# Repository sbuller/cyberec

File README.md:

# cyberec

Embedded Controller and BMS for Cyberdecks

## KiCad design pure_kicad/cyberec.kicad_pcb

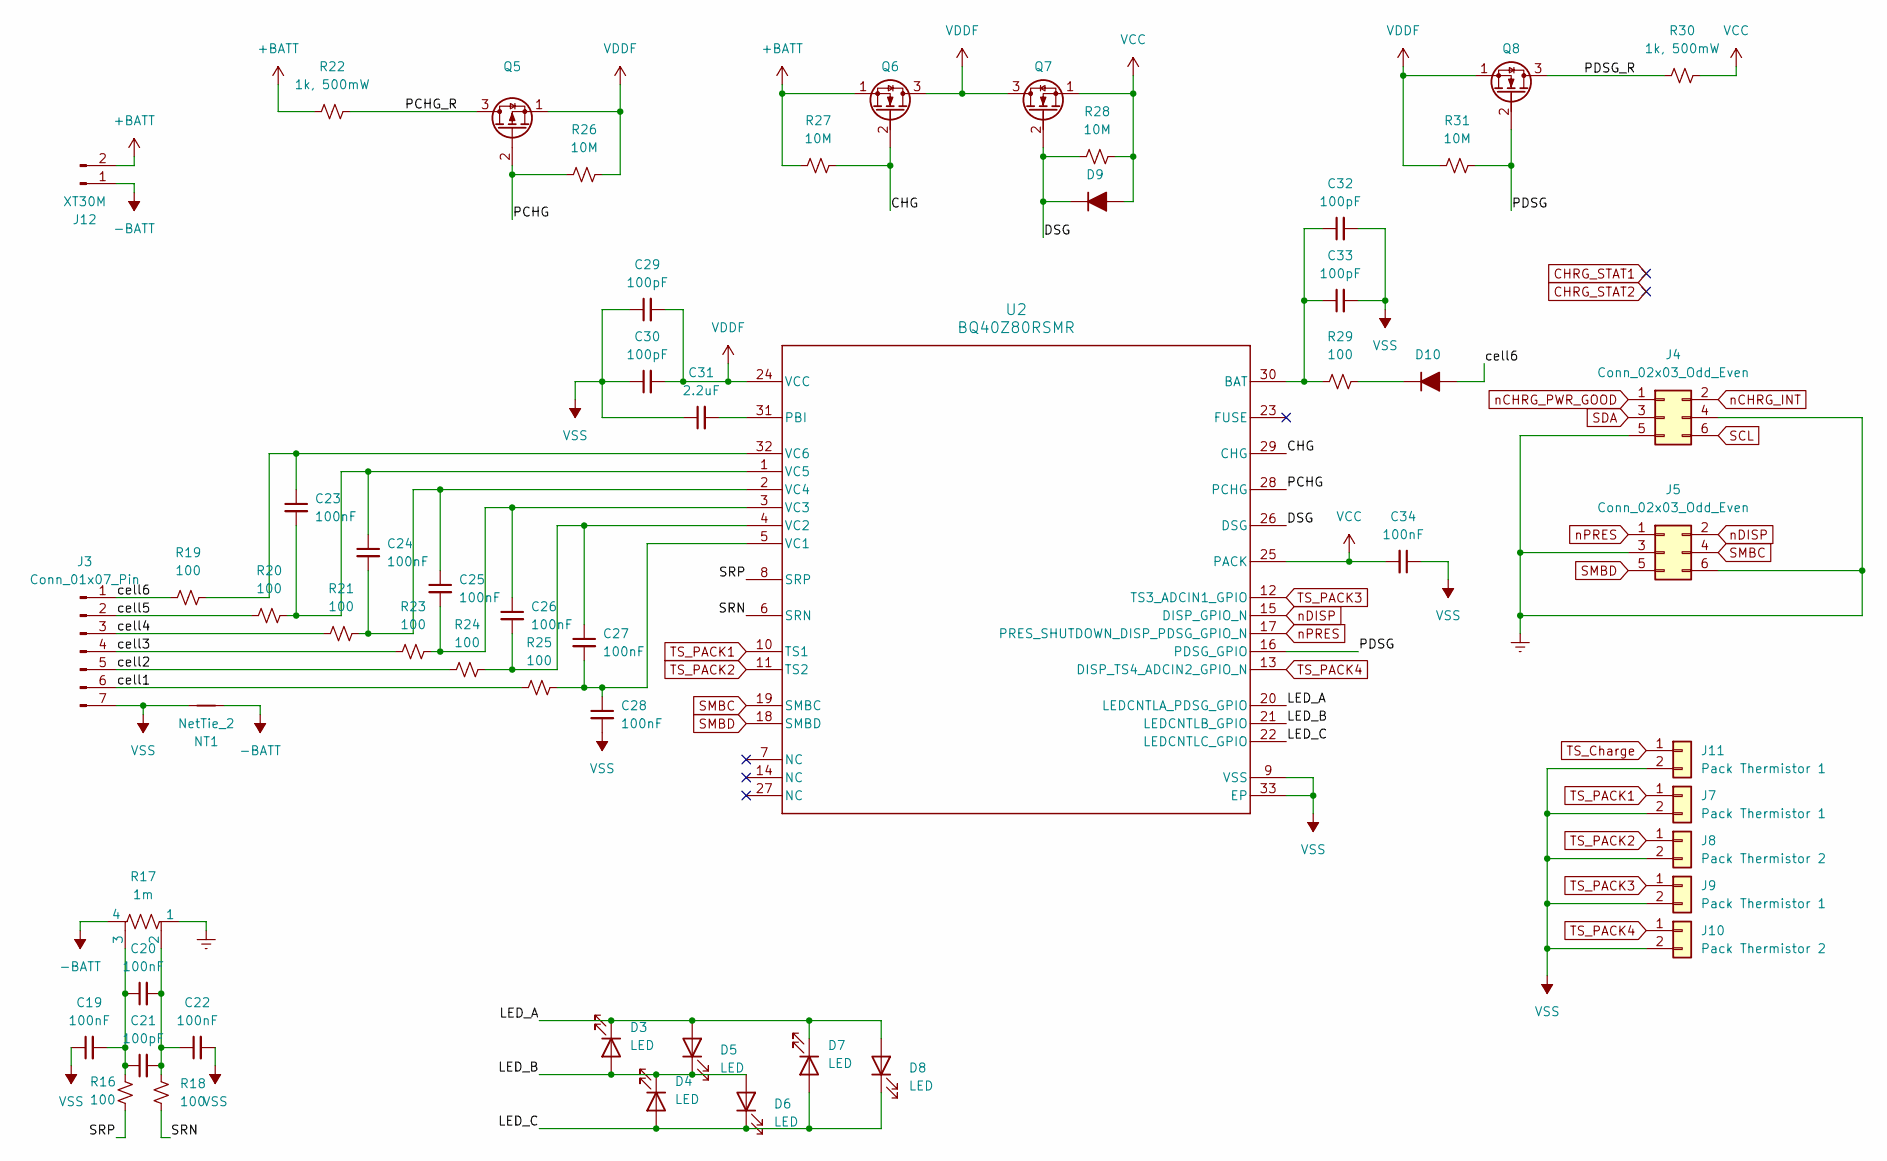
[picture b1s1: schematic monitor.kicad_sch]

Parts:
C19, C20, C22, C23, C24, C25, C26, C27, C28, C34: 100nF; C_0603_1608Metric_Pad1.08x0.95mm_HandSolder
C21, C29, C30, C32, C33: 100pF; C_0603_1608Metric_Pad1.08x0.95mm_HandSolder
C31: 2.2uF; C_0603_1608Metric_Pad1.08x0.95mm_HandSolder
D3, D4, D5, D6, D7, D8: LED; LED_0603_1608Metric_Pad1.05x0.95mm_HandSolder
D9, D10: 1N4001; D_SOD-123F
J3: Conn_01x07_Pin; JST_XH_B7B-XH-AM_1x07_P2.50mm_Vertical
J4, J5: Conn_02x03_Odd_Even; PinHeader_2x03_P1.27mm_Vertical
J7, J9, J11: Pack Thermistor 1; PinHeader_1x02_P2.00mm_Vertical
J8, J10: Pack Thermistor 2; PinHeader_1x02_P2.00mm_Vertical
J12: XT30M; AMASS_XT30U-M_1x02_P5.0mm_Vertical
NT1: NetTie_2; NetTie-2_SMD_Pad2.0mm
Q5: Q_PMOS_SGD; DFN-8_L3.0-W3.0-P0.65-BL-4
Q6, Q7, Q8: Q_NMOS_DGS; DFN-8_L3.0-W3.0-P0.65-BL-4
R16, R18, R19, R20, R21, R23, R24, R25, R29: 100; R_0603_1608Metric_Pad0.98x0.95mm_HandSolder
R17: 1m; R1206-sense-handsolder
R22, R30: 1k, 500mW; R_1210_3225Metric_Pad1.30x2.65mm_HandSolder
R26, R27, R28, R31: 10M; R_0402_1005Metric_Pad0.72x0.64mm_HandSolder
U2: BQ40Z80RSMR; RSM0032A-IPC_A

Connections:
+BATT: J12.2, Q6.1 (S), R22.2, R27.2
-BATT: J12.1, NT1.2, R17.4
/Battery Monitor/CHG: Q6.2 (G), R27.1, U2.29 (CHG)
/Battery Monitor/DSG: D9.1 (K), Q7.2 (G), R28.2, U2.26 (DSG)
/Battery Monitor/LED_A: D3.1 (K), D5.2 (A), D7.1 (K), D8.2 (A), U2.20 (LEDCNTLA_PDSG_GPIO)
/Battery Monitor/LED_B: D3.2 (A), D4.1 (K), D5.1 (K), D6.2 (A), U2.21 (LEDCNTLB_GPIO)
/Battery Monitor/LED_C: D4.2 (A), D6.1 (K), D7.2 (A), D8.1 (K), U2.22 (LEDCNTLC_GPIO)
/Battery Monitor/PCHG: Q5.2 (G), R26.2, U2.28 (PCHG)
/Battery Monitor/PCHG_R: Q5.3 (D), R22.1
/Battery Monitor/PDSG: Q8.2 (G), R31.1, U2.16 (PDSG_GPIO)
/Battery Monitor/PDSG_R: Q8.3 (D), R30.2
/Battery Monitor/SRN: R18.1, U2.6 (SRN)
/Battery Monitor/SRP: R16.1, U2.8 (SRP)
/Battery Monitor/cell1: J3.6, R25.2
/Battery Monitor/cell2: J3.5, R24.2
/Battery Monitor/cell3: J3.4, R23.2
/Battery Monitor/cell4: J3.3, R21.2
/Battery Monitor/cell5: J3.2, R20.2
/Battery Monitor/cell6: D10.2 (A), J3.1, R19.2
Earth: J4.4, J4.5, J5.3, J5.6, R17.1; also elsewhere on the board
unnamed: C19.2, C20.1, C21.1, R16.2, R17.3
unnamed: C20.2, C21.2, C22.1, R17.2, R18.2
unnamed: D10.1 (K), R29.1
unnamed: C32.1, C33.1, R29.2, U2.30 (BAT)
unnamed: C31.2, U2.31 (PBI)
unnamed: C27.2, C28.1, R25.1, U2.5 (VC1)
unnamed: C26.2, C27.1, R24.1, U2.4 (VC2)
unnamed: C25.2, C26.1, R23.1, U2.3 (VC3)
unnamed: C24.2, C25.1, R21.1, U2.2 (VC4)
unnamed: C23.2, C24.1, R20.1, U2.1 (VC5)
unnamed: C23.1, R19.1, U2.32 (VC6)
SCL: J4.6; also elsewhere on the board
SDA: J4.3; also elsewhere on the board
SMBC: J5.4, U2.19 (SMBC)
SMBD: J5.5, U2.18 (SMBD)
TS_Charge: J11.1; also elsewhere on the board
TS_PACK1: J7.1, U2.10 (TS1)
TS_PACK2: J8.1, U2.11 (TS2)
TS_PACK3: J9.1, U2.12 (TS3_ADCIN1_GPIO)
TS_PACK4: J10.1, U2.13 (DISP_TS4_ADCIN2_GPIO_N)
VCC: C34.2, D9.2 (A), Q7.1 (S), R28.1, R30.1, U2.25 (PACK); also elsewhere on the board
VDDF: C29.2, C30.2, Q5.1 (S), Q6.3 (D), Q7.3 (D), Q8.1 (S), R26.1, R31.2, U2.24 (VCC)
VSS: C19.1, C22.2, C28.2, C29.1, C30.1, C31.1, C32.2, C33.2, C34.1, J3.7, J7.2, J8.2, J9.2, J10.2, J11.2, NT1.1, U2.9 (VSS), U2.33 (EP)
nCHRG_INT: J4.2; also elsewhere on the board
nCHRG_PWR_GOOD: J4.1; also elsewhere on the board
nDISP: J5.2, U2.15 (DISP_GPIO_N)
nPRES: J5.1, U2.17 (PRES_SHUTDOWN_DISP_PDSG_GPIO_N)

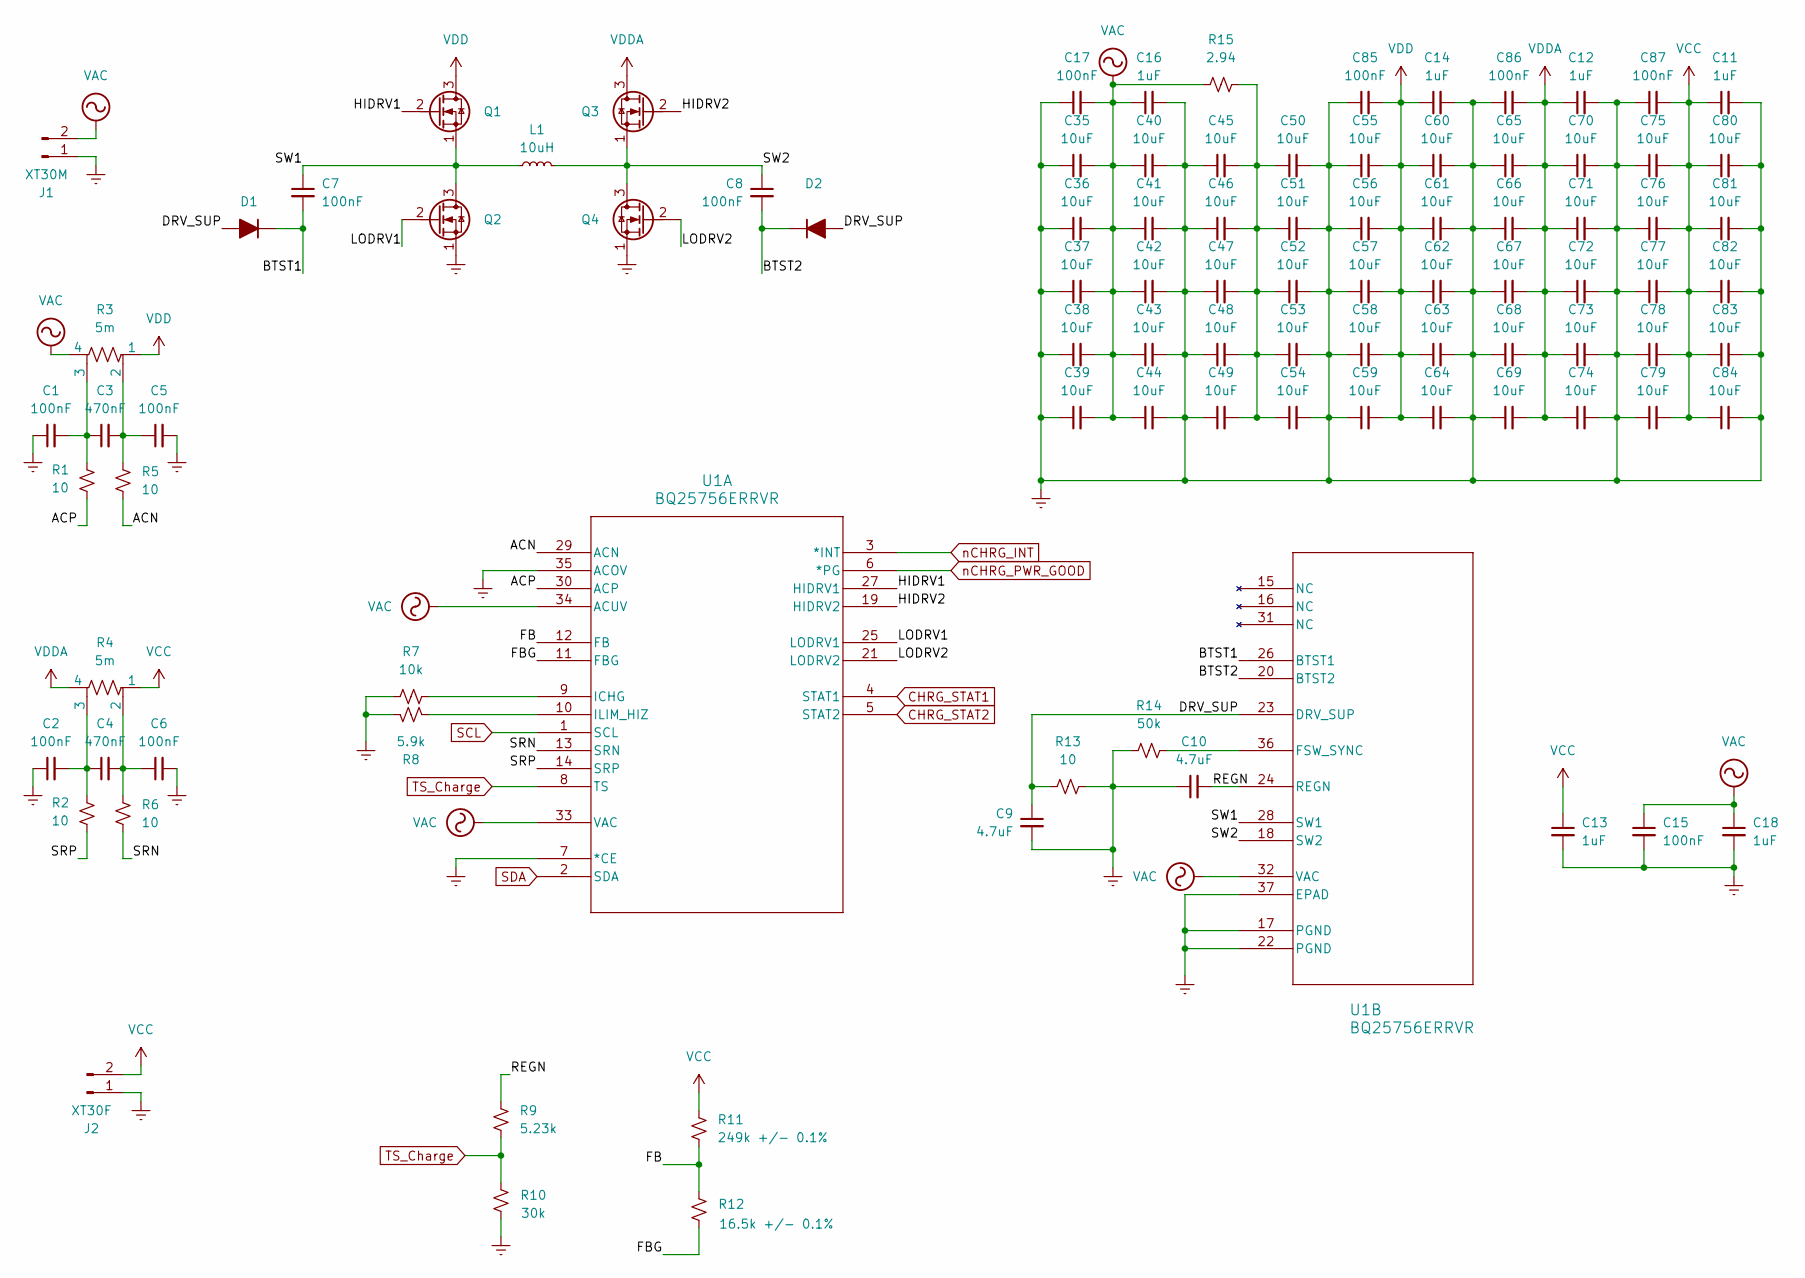
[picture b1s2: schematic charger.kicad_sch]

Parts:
C1, C2, C5, C6, C7, C8, C15, C17, C85, C86, C87: 100nF; C_0603_1608Metric_Pad1.08x0.95mm_HandSolder
C3, C4: 470nF; C_0603_1608Metric_Pad1.08x0.95mm_HandSolder
C9, C10: 4.7uF; C_0603_1608Metric_Pad1.08x0.95mm_HandSolder
C11, C12, C13, C14, C16, C18: 1uF; C_0603_1608Metric_Pad1.08x0.95mm_HandSolder
C35, C36, C37, C38, C39, C40, C41, C42, C43, C44, C45, C46, C47, C48, C49, C50, C51, C52, C53, C54, C55, C56, C57, C58, C59, C60, C61, C62, C63, C64, C65, C66, C67, C68, C69, C70, C71, C72, C73, C74, C75, C76, C77, C78, C79, C80, C81, C82, C83, C84: 10uF; C_1206_3216Metric_Pad1.33x1.80mm_HandSolder
D1, D2: PMEG2010BELD; D_SOD-882D
J1: XT30M; AMASS_XT30U-M_1x02_P5.0mm_Vertical
J2: XT30F; AMASS_XT30U-F_1x02_P5.0mm_Vertical
L1: 10uH; IND-SMD_L13.5-W12.6
Q1, Q2, Q3, Q4: Q_NMOS_DGS; DFN-8_L3.0-W3.0-P0.65-BL-4
R1, R2, R5, R6, R13: 10; R_0603_1608Metric_Pad0.98x0.95mm_HandSolder
R3, R4: 5m; R1206-sense-handsolder
R7: 10k; R_0603_1608Metric_Pad0.98x0.95mm_HandSolder
R8: 5.9k; R_0603_1608Metric_Pad0.98x0.95mm_HandSolder
R9: 5.23k; R_0603_1608Metric_Pad0.98x0.95mm_HandSolder
R10: 30k; R_0603_1608Metric_Pad0.98x0.95mm_HandSolder
R11: 249k +/- 0.1%; R_0603_1608Metric_Pad0.98x0.95mm_HandSolder
R12: 16.5k +/- 0.1%; R_0603_1608Metric_Pad0.98x0.95mm_HandSolder
R14: 50k; R_0402_1005Metric_Pad0.72x0.64mm_HandSolder
R15: 2.94; R_0603_1608Metric_Pad0.98x0.95mm_HandSolder
U1: BQ25756ERRVR; VQFN36_RRV_TEX

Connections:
/Charger/ACN: R5.1, U1.29 (ACN)
/Charger/ACP: R1.1, U1.30 (ACP)
/Charger/BTST1: C7.2, D1.1 (K), U1.26 (BTST1)
/Charger/BTST2: C8.2, D2.1 (K), U1.20 (BTST2)
/Charger/DRV_SUP: C9.1, D1.2 (A), D2.2 (A), R13.2, U1.23 (DRV_SUP)
/Charger/FB: R11.2, R12.1, U1.12 (FB)
/Charger/FBG: R12.2, U1.11 (FBG)
/Charger/HIDRV1: Q1.2 (G), U1.27 (HIDRV1)
/Charger/HIDRV2: Q3.2 (G), U1.19 (HIDRV2)
/Charger/LODRV1: Q2.2 (G), U1.25 (LODRV1)
/Charger/LODRV2: Q4.2 (G), U1.21 (LODRV2)
/Charger/REGN: C10.2, R9.1, U1.24 (REGN)
/Charger/SRN: R6.1, U1.13 (SRN)
/Charger/SRP: R2.1, U1.14 (SRP)
/Charger/SW1: C7.1, L1.1, Q1.1 (S), Q2.3 (D), U1.28 (SW1)
/Charger/SW2: C8.1, L1.2, Q3.1 (S), Q4.3 (D), U1.18 (SW2)
CHRG_STAT1: U1.4 (STAT1)
CHRG_STAT2: U1.5 (STAT2)
Earth: C1.1, C2.1, C5.2, C6.2, C9.2, C10.1, C11.2, C12.2, C13.2, C14.2, C15.2, C16.2, C17.1, C18.2, C35.1, C36.1, C37.1, C38.1, C39.1, C40.2, C41.2, C42.2, C43.2, C44.2, C45.1, C46.1, C47.1, C48.1, C49.1, C50.2, C51.2, C52.2, C53.2, C54.2, C55.1, C56.1, C57.1, C58.1, C59.1, C60.2, C61.2, C62.2, C63.2, C64.2, C65.1, C66.1, C67.1, C68.1, C69.1, C70.2, C71.2, C72.2, C73.2, C74.2, C75.1, C76.1, C77.1, C78.1, C79.1, C80.2, C81.2, C82.2, C83.2, C84.2, C85.1, C86.1, C87.1, J1.1, J2.1, Q2.1 (S), Q4.1 (S), R7.2, R8.2, R10.2, R13.1, R14.2, U1.7 (*CE), U1.17 (PGND), U1.22 (PGND), U1.35 (ACOV), U1.37 (EPAD); also elsewhere on the board
unnamed: C1.2, C3.1, R1.2, R3.3
unnamed: C2.2, C4.1, R2.2, R4.3
unnamed: C3.2, C5.1, R3.2, R5.2
unnamed: C4.2, C6.1, R4.2, R6.2
unnamed: C45.2, C46.2, C47.2, C48.2, C49.2, C50.1, C51.1, C52.1, C53.1, C54.1, R15.2
unnamed: R7.1, U1.9 (ICHG)
unnamed: R8.1, U1.10 (ILIM_HIZ)
unnamed: R14.1, U1.36 (FSW_SYNC)
SCL: U1.1 (SCL); also elsewhere on the board
SDA: U1.2 (SDA); also elsewhere on the board
TS_Charge: R9.2, R10.1, U1.8 (TS); also elsewhere on the board
VAC: C15.1, C16.1, C17.2, C18.1, C35.2, C36.2, C37.2, C38.2, C39.2, C40.1, C41.1, C42.1, C43.1, C44.1, J1.2, R3.4, R15.1, U1.32 (VAC), U1.33 (VAC), U1.34 (ACUV)
VCC: C11.1, C13.1, C75.2, C76.2, C77.2, C78.2, C79.2, C80.1, C81.1, C82.1, C83.1, C84.1, C87.2, J2.2, R4.1, R11.1; also elsewhere on the board
VDD: C14.1, C55.2, C56.2, C57.2, C58.2, C59.2, C60.1, C61.1, C62.1, C63.1, C64.1, C85.2, Q1.3 (D), R3.1
VDDA: C12.1, C65.2, C66.2, C67.2, C68.2, C69.2, C70.1, C71.1, C72.1, C73.1, C74.1, C86.2, Q3.3 (D), R4.4
nCHRG_INT: U1.3 (*INT); also elsewhere on the board
nCHRG_PWR_GOOD: U1.6 (*PG); also elsewhere on the board

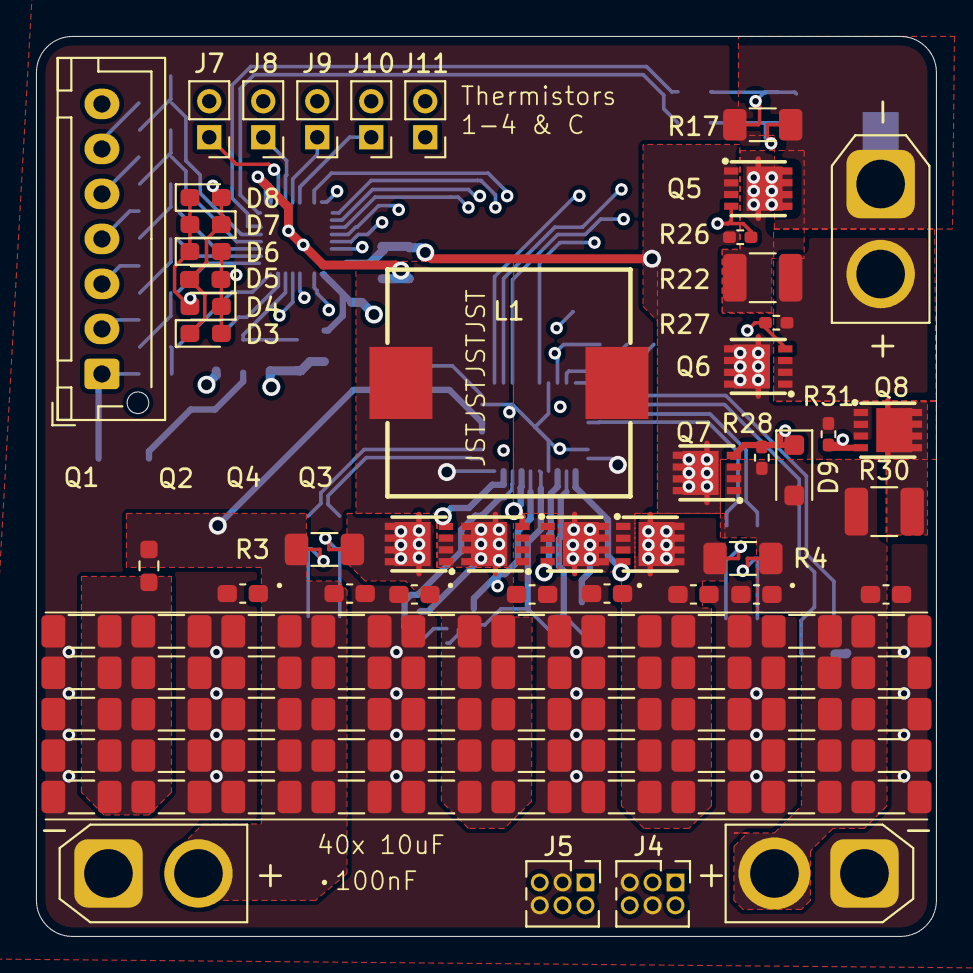
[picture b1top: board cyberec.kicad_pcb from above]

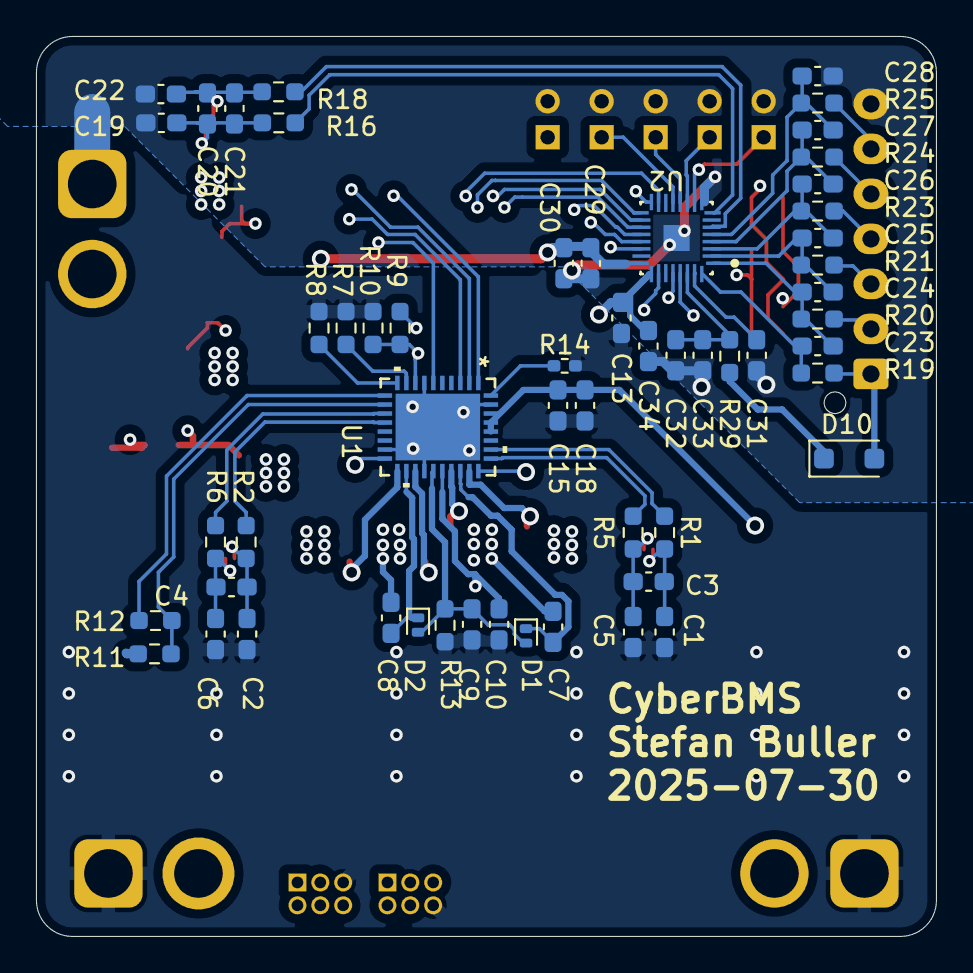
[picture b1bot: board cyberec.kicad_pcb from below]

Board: 4 copper layers, 50.0 x 50.0 mm, 151 parts (56 on the bottom side), 74 nets.

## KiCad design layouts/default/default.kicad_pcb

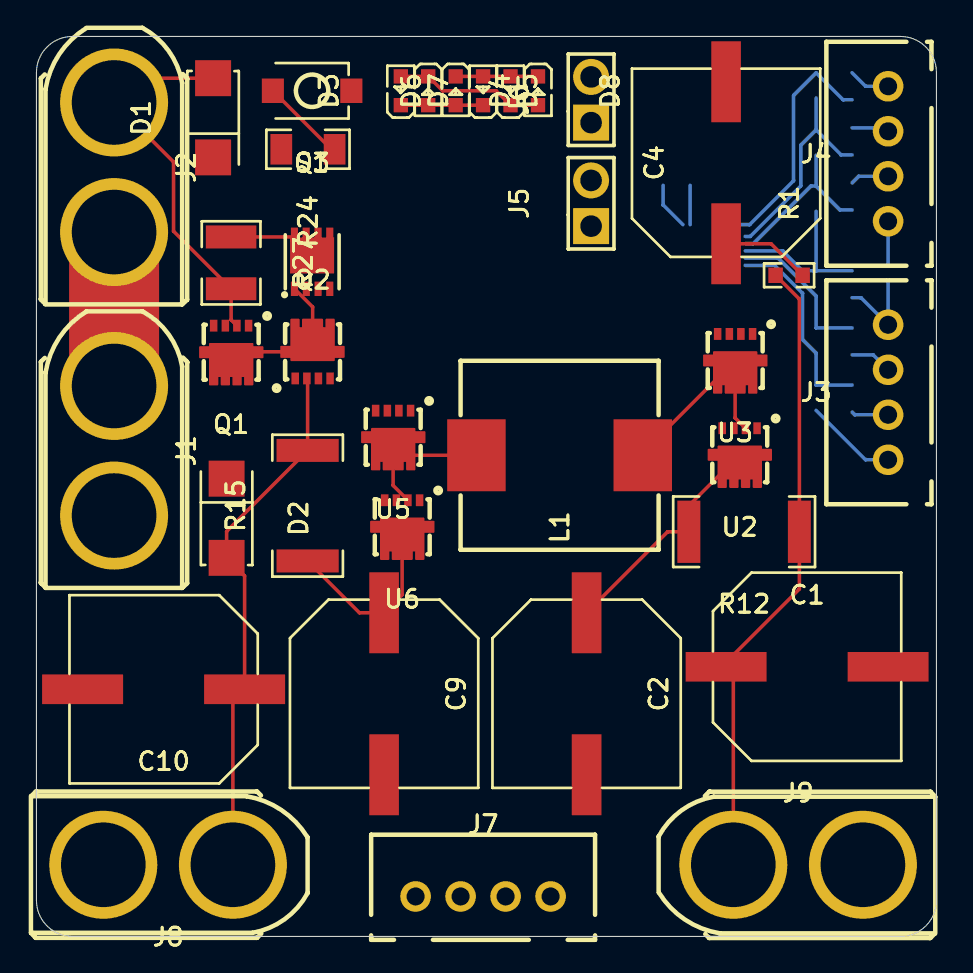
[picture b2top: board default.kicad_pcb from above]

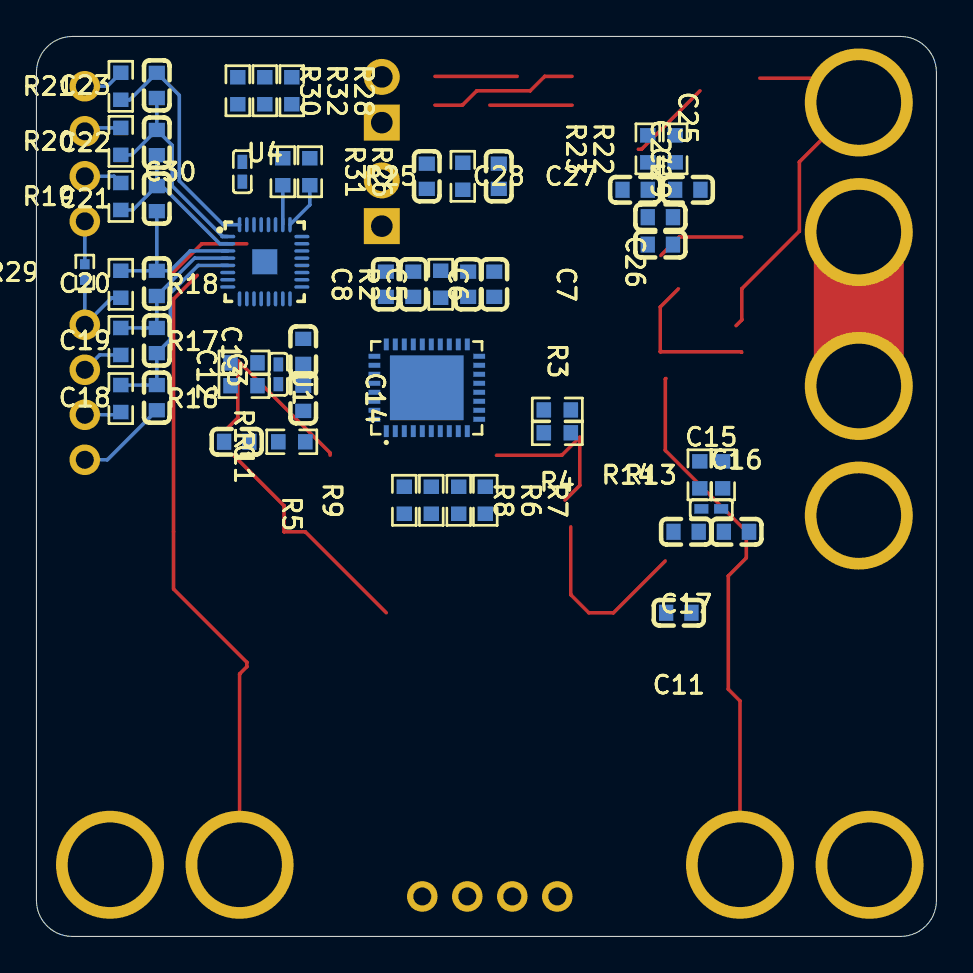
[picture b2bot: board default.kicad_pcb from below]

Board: 4 copper layers, 50.0 x 50.0 mm, 90 parts (54 on the bottom side), 62 nets.

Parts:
C1, C2, C4, C9, C10: CAP-SMD_BD10.0-L10.3-W10.3-FD
C3, C11: 1µF ±10% 50V X5R; C0603
C5, C8: 4.7µF ±10% 16V X5R; C0603
C6, C7, C13, C14, C16, C17, C18, C19, C20, C21, C22, C23, C25, C26, C29: 100nF ±10% 50V X7R; C0603
C12, C15: 470nF ±20% 16V X5R; C0402
C24, C27, C28: 100pF ±5% 50V C0G; C0603
C30: 2.2µF ±20% 6.3V X5R; C0402
D1, D2: SMA_L4.3-W2.6-LS5.2-RD
D3, D4, D5, D6, D7, D8: LED0603-RD
J1, J2, J8, J9: CONN-TH_XT60U-M
J3, J4, J7: CONN-TH_B4B-XH-A-LF-SN
J5, J6: HDR-TH_2P-P2.54-V-M
L1: IND-SMD_L11.0-W10.5_SL1050-330M
Q1, Q2: WDFN-5_L3.3-W3.3-P0.65-BL
Q3: DFN-8_L3.0-W3.0-P0.65-BL-4
R1: 2.94Ω ±1% 100mW; R0603
R2, R10, R11, R13, R14, R16, R17, R18, R19, R20, R21, R22, R23: 10Ω ±1% 100mW; R0603
R3: 16.5kΩ ±0% 100mW; R0603
R4: 249kΩ ±0% 100mW; R0603
R5: 50kΩ ±0% 100mW; R0603
R6, R26: 10kΩ ±1% 100mW; R0603
R7: 5.9kΩ ±1% 100mW; R0603
R8: 30kΩ ±1% 100mW; R0603
R9: 5.23kΩ ±1% 100mW; R0603
R12, R15: 5mΩ ±1% 2W; R2512
R24: 1mΩ ±1% 1W; R1206
R25, R28: 100Ω ±1% 100mW; R0603
R27: 1kΩ ±5% 500mW; R1210
R29: 0Ω 62.5mW; R0402
R30, R31, R32: 10MΩ ±1% 100mW; R0603
S1: SW-SMD_L3.9-W3.0-P4.45
U1: QFN-36_L5.0-W6.0-P0.50-TL-EP
U2, U3, U5, U6: WDFN-5_L3.3-W3.3-P0.65-BL
U4: VQFN-32_L4.0-W4.0-P0.40-TL-EP1.4

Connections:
-gnd: C1.2, C2.2, C3.2, C4.2, C5.2, C8.2, C9.2, C10.2, C11.2, C13.2, C14.2, C16.2, C17.2, J7.4, J8.1, J9.1, R5.2, R6.2, R7.2, R8.2, R22.2, R24.2, U1.7, U1.17, U1.22, U1.35, U1.37, U3.1, U3.2, U3.3, U5.1, U5.2, U5.3
-pos: C1.1, C3.1, J9.2, R1.1, R11.2, R12.1, U1.32, U1.33, U1.34
ACN: C12.2, C13.1, R10.1, U1.29
ACP: C12.1, C14.1, R11.1, U1.30
BAT: C27.1, C28.1, R25.2, U4.30
CHG: Q1.4, R30.2, R32.2, U4.29
FB: R3.1, R4.2, U1.12
FBG: R3.2, U1.11
FSW_SYNC: R5.1, U1.36
ICHG: R6.1, U1.9
ILIM_HIZ: R7.1, U1.10
PACK: R26.2, U4.25
PBI: C30.1, U4.31
PCHG: Q3.4, U4.28
REGN: C8.1, R2.2, R9.1, U1.24
S: C6.2, L1.1, U1.28, U2.1, U2.2, U2.3, U3.5
SCL: J7.2, U1.1, U4.19
SDA: J7.3, U1.2, U4.18
TS: R8.1, R9.2, U1.8
TS1: J5.1, U4.10
TS2: J6.1, U4.11
VC1: C18.2, C19.1, R16.1, U4.5
VC2: C19.2, C20.1, R17.1, U4.4
VC3: C20.2, C21.1, R18.1, U4.3
VC4: C21.2, C22.1, R19.1, U4.2
VC5: C22.2, C23.1, R20.1, U4.1
VC6: C23.2, R21.1, U4.32
VCC: R28.2, U4.24
charger-D: C7.2, L1.2, U1.18, U5.5, U6.1, U6.2, U6.3
charger-G-0: U1.27, U2.4
charger-G-1: U1.19, U6.4
charger-G-2: U1.25, U3.4
charger-G-3: U1.21, U5.4
charger-SRN: C15.2, C16.1, R13.1, U1.13
charger-SRP: C15.1, C17.1, R14.1, U1.14
charger-anode: C5.1, R2.1, U1.23
charger-cathode-0: C6.1, U1.26
charger-cathode-1: C7.1, U1.20
charger-pos-0: C2.1, R10.2, R12.2, U2.5
charger-pos-1: C4.1, R1.2
charger-pos-2: C9.1, C11.1, R14.2, R15.1, U6.5
nDISP_TS4_ADCIN2_GPIO: S1.1, U4.13
pack-D-0: Q1.5, Q2.5, Q3.1, Q3.2, Q3.3, R28.1, R32.1
pack-D-1: Q3.5, Q3.6, Q3.7, Q3.8, Q3.9, R27.1
pack-SRN: C24.2, C25.1, C29.2, R22.1, U4.6
pack-SRP: C24.1, C26.1, C29.1, R23.1, U4.8
pack-anode: D3.2, D4.1, D7.1, D8.2, U4.20
pack-c1-0: J3.3, R16.2
pack-c1-1: J4.3, R19.2
pack-c2-0: J3.2, R17.2
pack-c2-1: J4.2, R20.2
pack-c3-0: J3.1, R18.2, R29.1
pack-c3-1: J4.1, R21.2
pack-cathode-0: D1.1, R25.1
pack-cathode-1: D2.1, Q2.4, R31.2, U4.26
pack-cathode-2: D3.1, D4.2, D5.2, D6.1, U4.21
pack-cathode-3: D5.1, D6.2, D7.2, D8.1, U4.22
pack-gnd-0: C18.1, C25.2, C26.2, C27.2, C28.2, C30.2, J1.1, J3.4, J5.2, J6.2, R23.2, R24.1, S1.2, U4.9, U4.23, U4.33
pack-gnd-1: J4.4, R29.2
pack-gnd-2: J1.2, J2.1
vbat: D1.2, J2.2, Q1.1, Q1.2, Q1.3, R27.2, R30.1
vsys: C10.1, D2.2, J8.2, Q2.1, Q2.2, Q2.3, R4.1, R13.2, R15.2, R26.1, R31.1

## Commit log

2025-07-11 Get the BQ25756 laid out
2025-07-11 Start work on battery pack
2025-07-12 Remove github workflows
2025-07-12 Make a start on BQ40Z80
2025-07-14 Some work on the battery monitor
2025-07-14 Fix README
2025-07-14 Some more work on fuel gauge
2025-07-16 Uh. Stuff
2025-07-18 Work on battery monitor
2025-07-18 Some thoughts about where to go
2025-07-23 join monitor and charger
2025-07-23 Add connectors for Power in/out, and I2C
2025-07-23 What if 50x50 was enough?
2025-07-24 Try out a 4 layer stackup within 50x50
2025-07-24 I think I've learned what I can of atopile. I'm losing hope
2025-07-24 Charger Schematic
2025-07-24 Add battery monitor schematic
2025-07-25 Assign parts, start layout
2025-07-25 Layout starting to look alright
2025-07-25 Import all the footprints, use project local 3d files
2025-07-25 Do most top side zones
2025-07-25 It seems that the charger needs to move.
2025-07-26 So, 10u X5Rs are a thing. Just use 40 of them
2025-07-26 Layout is mostly good. Still need i2c and stuff
2025-07-28 I think this was just sorting LEDs
2025-07-28 So, I've done the BMS portion, what next?
2025-07-28 Re-layout top side. Bottom to follow
2025-07-29 Most of the layout/routing on the back side
2025-07-29 I think the routing so far is done. I've started collecting signals to route off the board
2025-07-29 Switch to single xt30 and JST B7B for pack, and add thermistor headers
2025-07-29 Added so many pins
2025-07-29 Remove lock file
2025-07-30 Move IO to bottom edge, clean up routing, labels
